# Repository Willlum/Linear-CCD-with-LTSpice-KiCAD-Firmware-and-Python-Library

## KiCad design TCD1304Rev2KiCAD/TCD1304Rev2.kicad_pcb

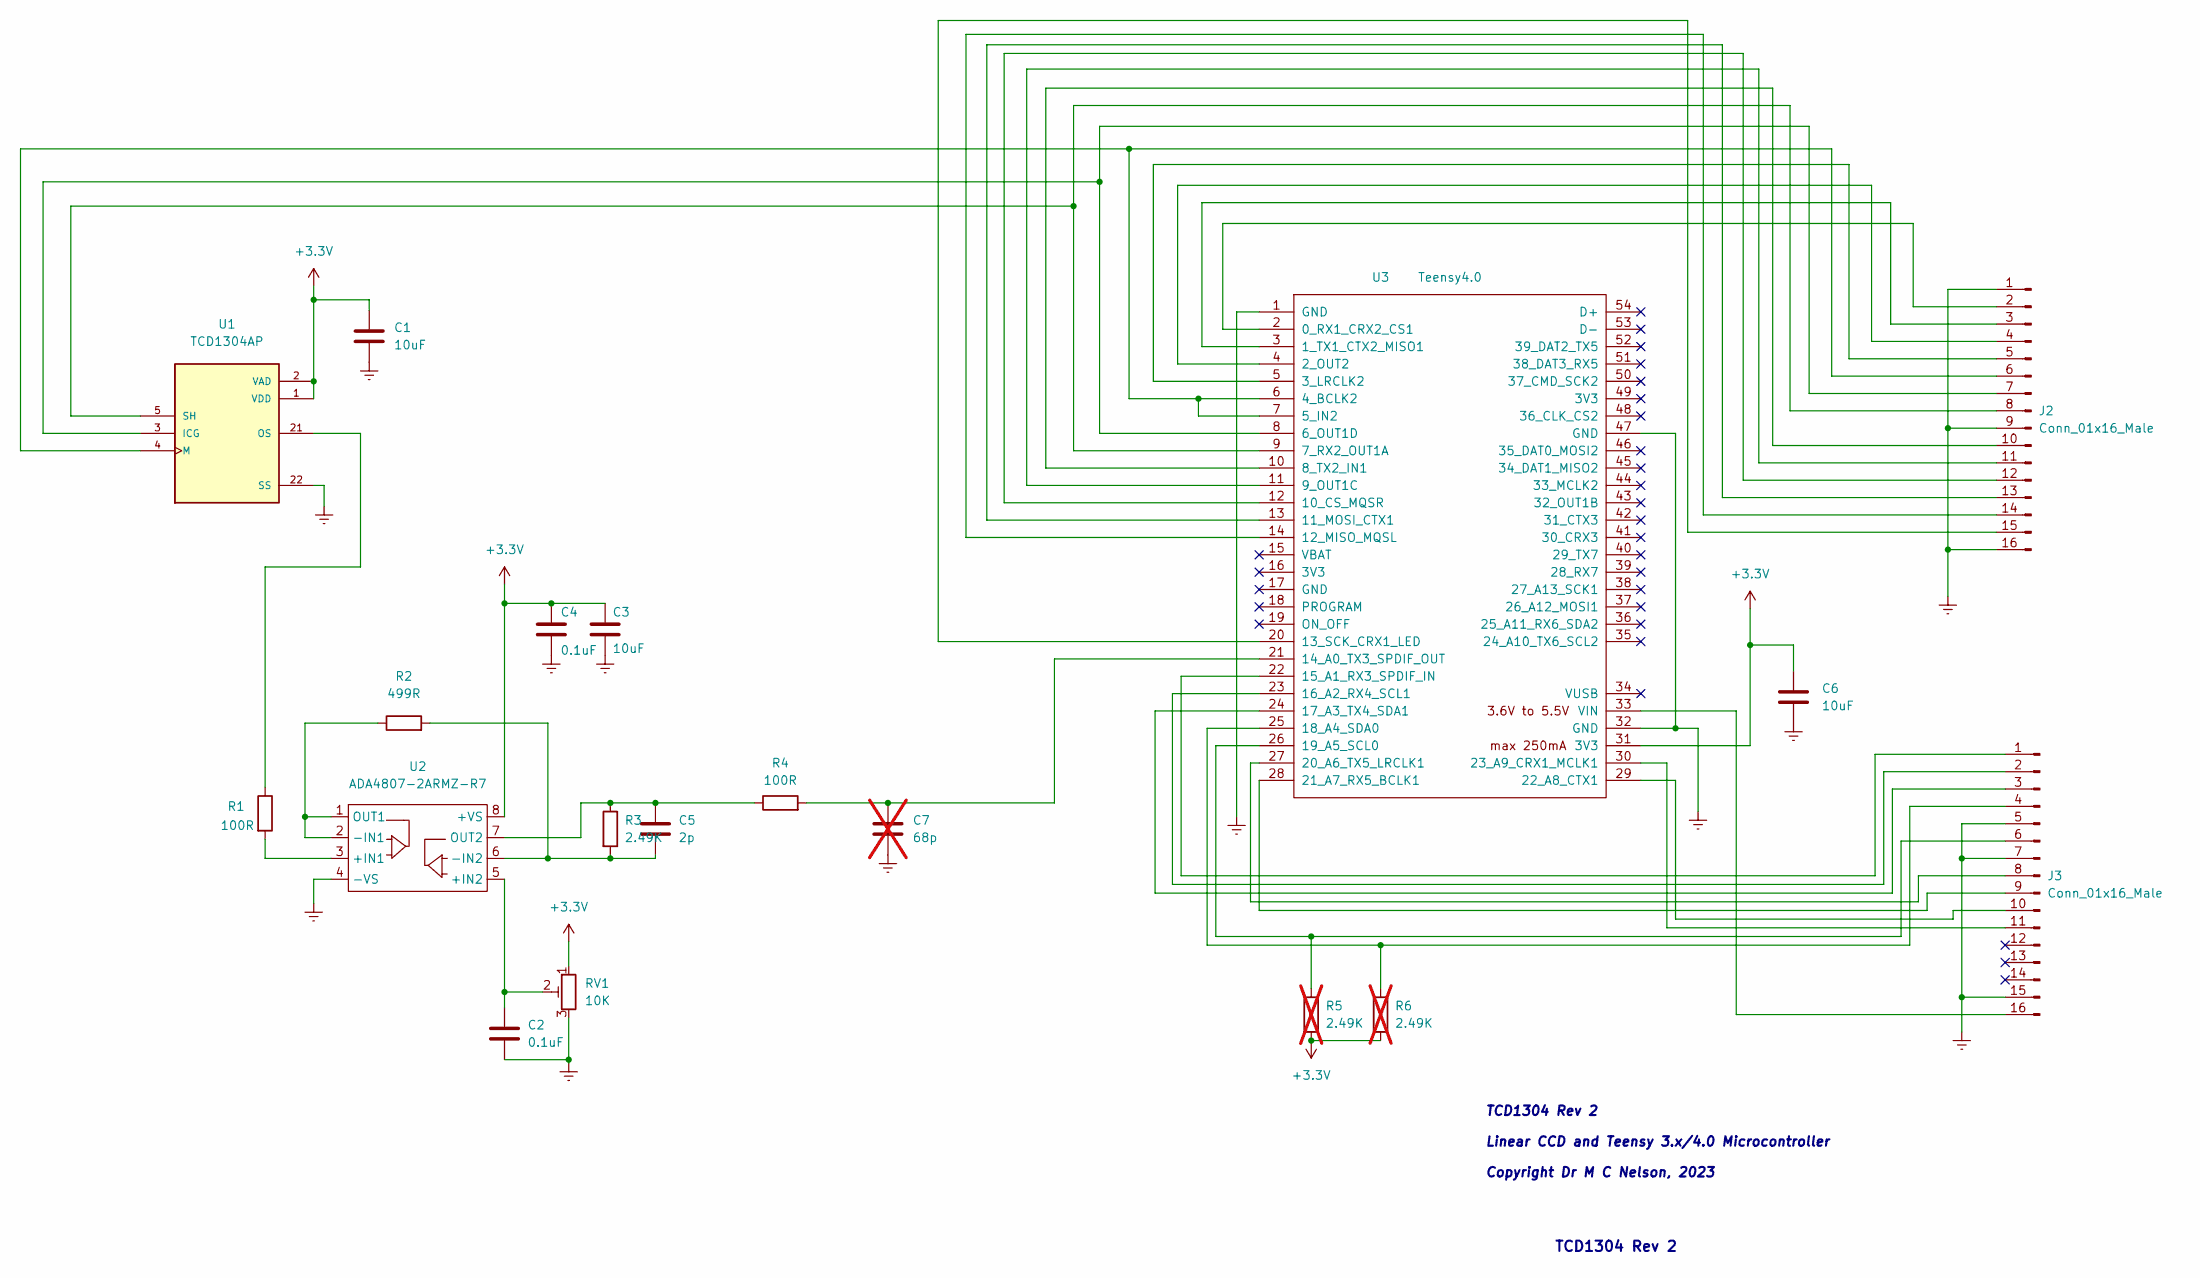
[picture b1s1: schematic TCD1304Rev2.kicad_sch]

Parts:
C1, C3, C6: 10uF; C_0805_2012Metric_Pad1.18x1.45mm_HandSolder; Digikey 490-12317-1-ND
C2, C4: 0.1uF; C_0805_2012Metric_Pad1.18x1.45mm_HandSolder; Digikey 399-C0603X104J3RACAUTOCT-ND
C5: 2p; C_0805_2012Metric_Pad1.18x1.45mm_HandSolder; Digikey 1284-1196-1-ND
C7: 68p; C_0805_2012Metric_Pad1.18x1.45mm_HandSolder; Digikey 1276-1135-1-ND; not fitted
J2, J3: Conn_01x16_Male; PinHeader_1x16_P2.54mm_Vertical; Digikey 3M156268-16-ND
R1, R4: 100R; R_0805_2012Metric_Pad1.20x1.40mm_HandSolder; Digikey 2019-RK73H1JTTD1000FCT-ND
R2: 499R; R_0805_2012Metric_Pad1.20x1.40mm_HandSolder; Digikey 2019-RK73H1JTTD4990FCT-ND
R3: 2.49K; R_0805_2012Metric_Pad1.20x1.40mm_HandSolder; Digikey 311-2.49KHRCT-ND
R5, R6: 2.49K; R_0805_2012Metric_Pad1.20x1.40mm_HandSolder; Digikey 311-2.49KHRCT-ND; not fitted
RV1: 10K; TRIM_3296W-1-502LF; Digikey 3296W-103LF-ND
U1: TCD1304AP; DIP1016W47P254L4210H372Q22; Digikey 110-87-422-41-001101
U2: ADA4807-2ARMZ-R7; MSOP-8_3x3mm_P0.65mm; Digikey ADA4807-2ARMZ-R7CT-ND
U3: Teensy4.0; Teensy40; Digikey 1568-DEV-16997-ND

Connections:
+3.3V: C1.1, C3.1, C4.1, C6.1, R5.2, R6.2, RV1.1, U1.1 (VDD), U1.2 (VAD), U2.8 (+VS), U3.31 (3V3)
Earth: C1.2, C2.2, C3.2, C4.2, C6.2, C7.2, J2.1, J2.9, J2.16, J3.5, J3.7, J3.15, RV1.3, U1.22 (SS), U2.4 (-VS), U3.1 (GND), U3.32 (GND), U3.47 (GND)
unnamed: J2.2, U3.2 (0_RX1_CRX2_CS1)
unnamed: J2.3, U3.3 (1_TX1_CTX2_MISO1)
unnamed: J2.4, U3.4 (2_OUT2)
unnamed: J2.5, U3.5 (3_LRCLK2)
unnamed: J2.6, U1.4 (M), U3.6 (4_BCLK2), U3.7 (5_IN2)
unnamed: J2.7, U1.3 (ICG), U3.8 (6_OUT1D)
unnamed: J2.8, U1.5 (SH), U3.9 (7_RX2_OUT1A)
unnamed: J2.10, U3.10 (8_TX2_IN1)
unnamed: J2.11, U3.11 (9_OUT1C)
unnamed: J2.12, U3.12 (10_CS_MQSR)
unnamed: J2.13, U3.13 (11_MOSI_CTX1)
unnamed: J2.14, U3.14 (12_MISO_MQSL)
unnamed: J2.15, U3.20 (13_SCK_CRX1_LED)
unnamed: J3.1, U3.22 (15_A1_RX3_SPDIF_IN)
unnamed: J3.2, U3.23 (16_A2_RX4_SCL1)
unnamed: J3.3, U3.24 (17_A3_TX4_SDA1)
unnamed: J3.4, R6.1, U3.25 (18_A4_SDA0)
unnamed: J3.6, R5.1, U3.26 (19_A5_SCL0)
unnamed: J3.8, U3.27 (20_A6_TX5_LRCLK1)
unnamed: J3.9, U3.28 (21_A7_RX5_BCLK1)
unnamed: J3.10, U3.29 (22_A8_CTX1)
unnamed: J3.11, U3.30 (23_A9_CRX1_MCLK1)
unnamed: J3.16, U3.33 (VIN)
unnamed: R1.1, U1.21 (OS)
unnamed: R1.2, U2.3 (+IN1)
unnamed: C2.1, RV1.2, U2.5 (+IN2)
unnamed: R2.1, U2.1 (OUT1), U2.2 (-IN1)
unnamed: C5.2, R2.2, R3.2, U2.6 (-IN2)
unnamed: C5.1, R3.1, R4.1, U2.7 (OUT2)
unnamed: C7.1, R4.2, U3.21 (14_A0_TX3_SPDIF_OUT)

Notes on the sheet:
TCD1304 Rev 2 Linear CCD and Teensy 3.x/4.0 Microcontroller Copyright Dr M C Nelson, 2023
TCD1304 Rev 2

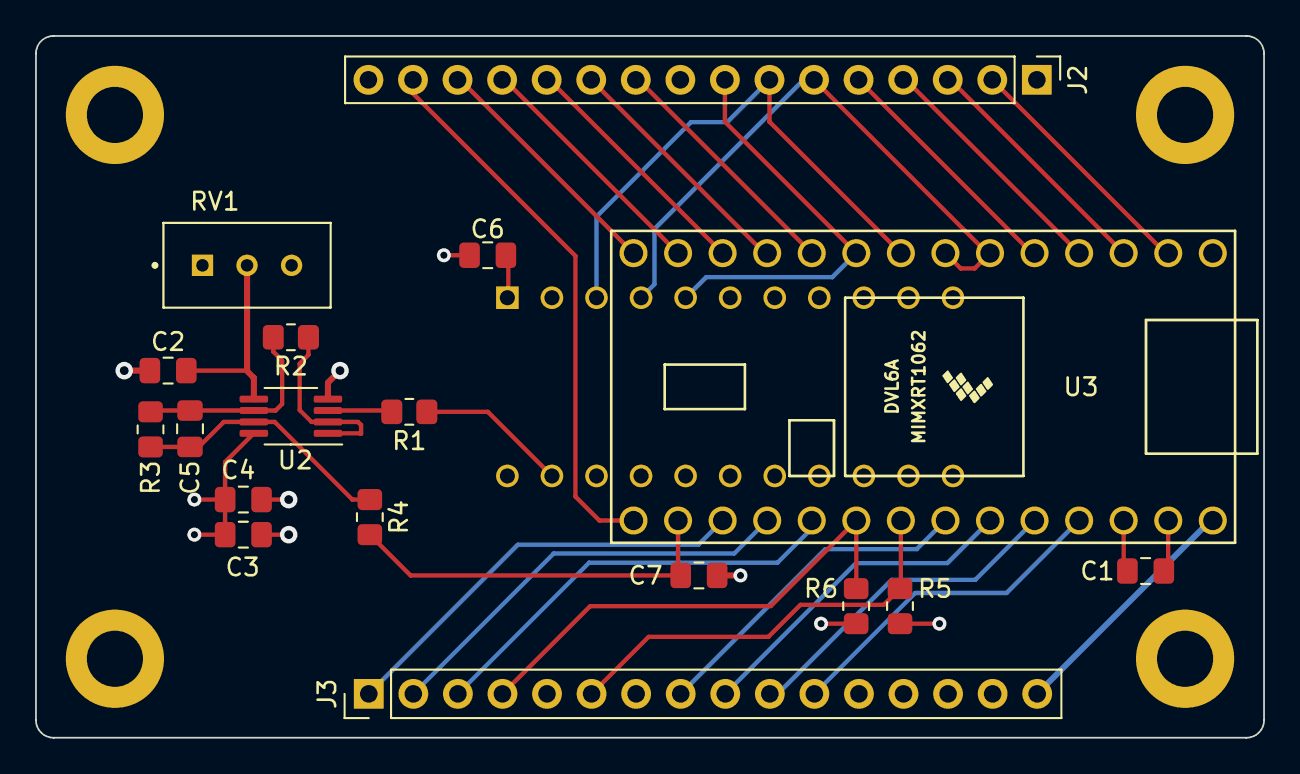
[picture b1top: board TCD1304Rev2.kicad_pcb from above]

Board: 4 copper layers, 70.0 x 40.0 mm, 19 parts (1 on the bottom side), 32 nets.

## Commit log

2025-10-06 updated pcb
2026-01-20 pcb changes
2026-02-01 added data sheet for TCD sensor
2026-06-01 Add halfWidthMin.py to analyze and visualize rectangular pulse signals
    - Implemented a script to generate a noisy baseline signal with two rectangular pulses having sloped edges.
    - Utilized scipy's find_peaks to identify peaks and calculate inner wall distances.
    - Added functionality to compute and display the gap width in both sample indices and millimeters.
    - Included a plot to visualize the generated signal and highlight key features such as inner edges and center.
2026-06-02 Add utility functions and data model classes for TCD1304 CCD measurements
    - Introduced utility functions in `utils.py` for string parsing, data generation, and I/O operations.
    - Implemented `LccdFrame` and `LccdData` classes in `data_models.py` to handle CCD measurement frames and data file parsing.
    - Added methods for loading, parsing, and organizing frame data, including support for wavelength calibration.
    - Enhanced error handling and debugging capabilities in the data model classes.
2026-06-02 Add find_device.sh script to list available serial ports and USB devices
2026-06-02 Add struct module import for data handling in TCD1304Rev2Controller
2026-06-02 Add clock configuration entries to tcd1304rev2controller.history
2026-06-02 Refactor TCD1304Rev2Controller metadata and update clock configuration history
2026-06-02 Add Light Meter guide and example usage for TCD1304 CCD sensor
2026-06-02 Copilot CLI session 7157efc6-ba09-4ee3-917d-32ea250e7bf7 changes
2026-06-02 init commit
2026-06-05 changed file name
